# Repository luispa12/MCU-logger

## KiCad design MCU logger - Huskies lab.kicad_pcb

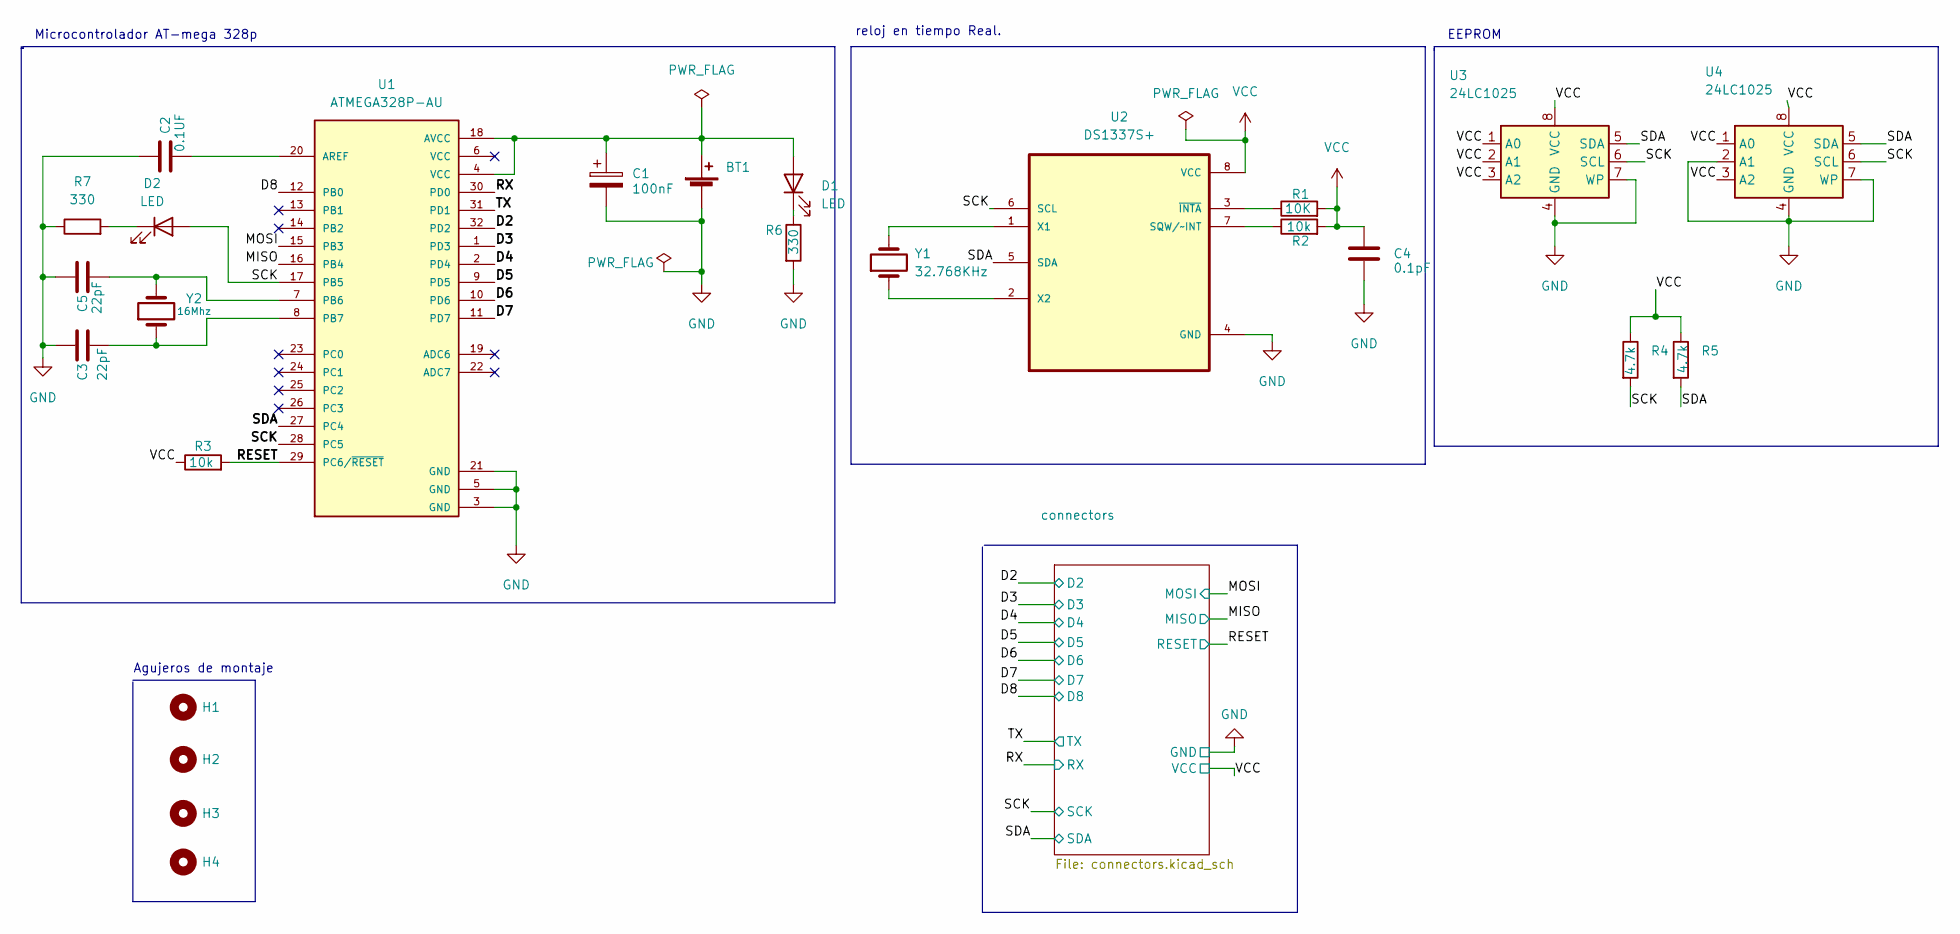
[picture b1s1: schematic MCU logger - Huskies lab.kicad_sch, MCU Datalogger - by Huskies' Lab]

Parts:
BT1: Battery_Cell; PinHeader_1x02_P2.54mm_Vertical
C1: 100nF; C_0805_2012Metric
C2: 0.1UF; C_0805_2012Metric
C3, C5: 22pF; C_0805_2012Metric
C4: 0.1pF; C_0805_2012Metric
D1, D2: LED; LED_0805_2012Metric
H1, H2, H3, H4: MountingHole; MountingHole_2.1mm
R1, R3: 10k; R_0805_2012Metric_Pad1.20x1.40mm_HandSolder
R2: 10K; R_0805_2012Metric_Pad1.20x1.40mm_HandSolder
R4, R5: 4.7k; R_0805_2012Metric_Pad1.20x1.40mm_HandSolder
R6, R7: 330; R_0805_2012Metric_Pad1.20x1.40mm_HandSolder
U1: ATMEGA328P-AU; QFP80P900X900X120-32N
U2: DS1337S+; SOIC127P600X175-8N
U3, U4: 24LC1025; SOIC-8_5.23x5.23mm_P1.27mm
Y1: 32.768KHz; Crystal_HC49-U_Vertical
Y2: 16Mhz; Crystal_HC49-U_Vertical

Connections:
/D2: U1.32 (PD2); also elsewhere on the board
/D3: U1.1 (PD3); also elsewhere on the board
/D4: U1.2 (PD4); also elsewhere on the board
/D5: U1.9 (PD5); also elsewhere on the board
/D6: U1.10 (PD6); also elsewhere on the board
/D7: U1.11 (PD7); also elsewhere on the board
/D8: U1.12 (PB0); also elsewhere on the board
/MISO: U1.16 (PB4); also elsewhere on the board
/MOSI: U1.15 (PB3); also elsewhere on the board
/RESET: R3.2, U1.29 (PC6/~RESET); also elsewhere on the board
/RX: U1.30 (PD0); also elsewhere on the board
/SCK: D2.2 (A), R4.2, U1.17 (PB5), U1.28 (PC5), U2.6 (SCL), U3.6 (SCL), U4.6 (SCL); also elsewhere on the board
/SDA: R5.2, U1.27 (PC4), U2.5 (SDA), U3.5 (SDA), U4.5 (SDA); also elsewhere on the board
/TX: U1.31 (PD1); also elsewhere on the board
GND: BT1.2 (-), C1.2, C2.1, C3.1, C4.2, C5.1, R6.2, R7.1, U1.3 (GND), U1.5 (GND), U1.21 (GND), U2.4 (GND), U3.4 (GND), U3.7 (WP), U4.2 (A1), U4.4 (GND), U4.7 (WP); also elsewhere on the board
unnamed: BT1.1 (+), C1.1, D1.2 (A), U1.4 (VCC), U1.18 (AVCC)
unnamed: C2.2, U1.20 (AREF)
unnamed: C3.2, U1.8 (PB7), Y2.1
unnamed: C5.2, U1.7 (PB6), Y2.2
unnamed: D1.1 (K), R6.1
unnamed: D2.1 (K), R7.2
unnamed: R1.1, U2.7 (SQW/~INT)
unnamed: R2.1, U2.3 (~INTA)
unnamed: U2.1 (X1), Y1.2
unnamed: U2.2 (X2), Y1.1
VCC: C4.1, R1.2, R2.2, R3.1, R4.1, R5.1, U2.8 (VCC), U3.1 (A0), U3.2 (A1), U3.3 (A2), U3.8 (VCC), U4.1 (A0), U4.3 (A2), U4.8 (VCC); also elsewhere on the board

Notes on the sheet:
Agujeros de montaje
Microcontrolador AT-mega 328p
EEPROM
reloj en tiempo Real.

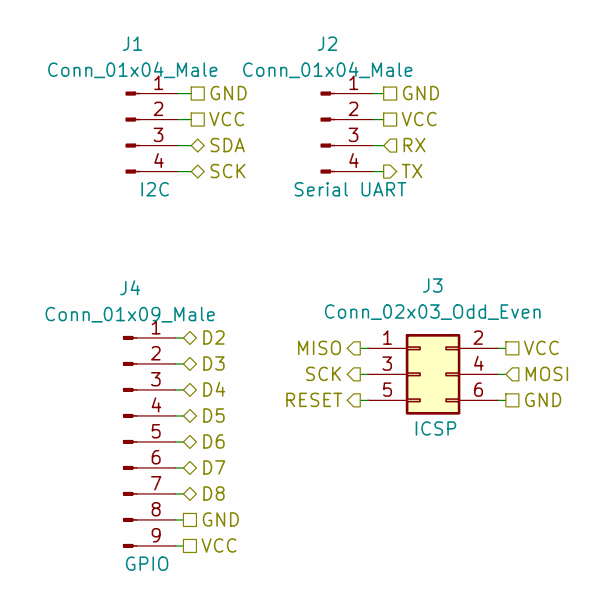
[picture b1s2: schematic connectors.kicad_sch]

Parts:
J1, J2: Conn_01x04_Male; PinHeader_1x04_P2.54mm_Vertical
J3: Conn_02x03_Odd_Even; PinHeader_2x03_P2.54mm_Vertical
J4: Conn_01x09_Male; PinHeader_1x09_P2.54mm_Vertical

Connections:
/D2: J4.1; also elsewhere on the board
/D3: J4.2; also elsewhere on the board
/D4: J4.3; also elsewhere on the board
/D5: J4.4; also elsewhere on the board
/D6: J4.5; also elsewhere on the board
/D7: J4.6; also elsewhere on the board
/D8: J4.7; also elsewhere on the board
/MISO: J3.1; also elsewhere on the board
/MOSI: J3.4; also elsewhere on the board
/RESET: J3.5; also elsewhere on the board
/RX: J2.3; also elsewhere on the board
/SCK: J1.4, J3.3; also elsewhere on the board
/SDA: J1.3; also elsewhere on the board
/TX: J2.4; also elsewhere on the board
GND: J1.1, J2.1, J3.6, J4.8; also elsewhere on the board
VCC: J1.2, J2.2, J3.2, J4.9; also elsewhere on the board

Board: 2 copper layers, 29 parts (0 on the bottom side), 26 nets, no tracks yet.

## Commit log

2022-12-28 set of the eeschema for the current project
2022-12-28 added the components required for the schematic
2022-12-28 couple more modifications to the schematic
2022-12-29 last changes
2022-12-29 test changes
2022-12-29 values of the componenents added.
2022-12-30 added the symbols anb the footprints to every component
2022-12-30 wiring of clock and EEPROM
2023-01-07 wiring of the first sheet completed
2023-01-24 modificaciones en los nombres de los conectores
2023-01-24 cableado c asi terminado, dos error aun
2023-01-31 cambio de nombre a las etiquetas, de Vcc a VCC, para que todas las etiquetas tengan el mismo nombre
2023-01-31 asignacion de las net labels de power a VCC y GND
2023-01-31 senalizacion del esquematico.
2023-01-31 configuracion del layout
2023-01-31 colocacion de los componentes terminada
